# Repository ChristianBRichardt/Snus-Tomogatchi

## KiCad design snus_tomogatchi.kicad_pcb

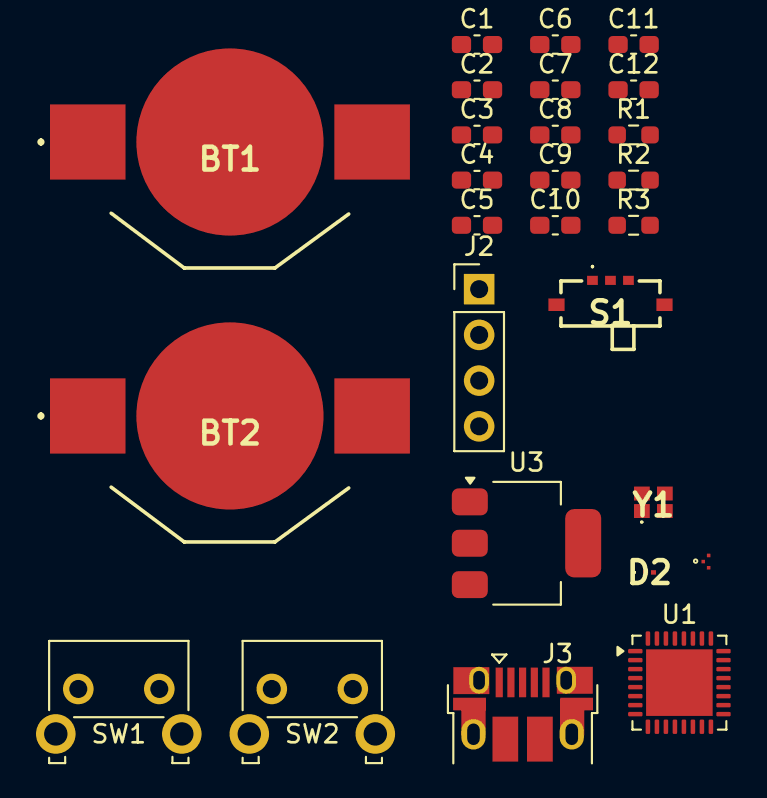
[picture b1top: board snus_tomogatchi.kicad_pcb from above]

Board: 2 copper layers, 27 parts (0 on the bottom side), 15 nets, no tracks yet.

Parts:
BT1, BT2: Battery_Cell; BATHLD007SMTTR
C1, C3, C4, C12: 10uF; C_0603_1608Metric_Pad1.08x0.95mm_HandSolder
C2, C5, C6, C11: 0.1uF; C_0603_1608Metric_Pad1.08x0.95mm_HandSolder
C7: 1uf; C_0603_1608Metric_Pad1.08x0.95mm_HandSolder
C8, C9: C_Small; C_0603_1608Metric_Pad1.08x0.95mm_HandSolder
C10: 1uF; C_0603_1608Metric_Pad1.08x0.95mm_HandSolder
D1: ESD122DMXR; DMX0003A
D2: ESD441DPLR
J2: Conn_01x04; PinHeader_1x04_P2.54mm_Vertical
J3: USB_B_Micro; USB_Micro-B_Amphenol_10103594-0001LF_Horizontal
R1: 10k; R_0603_1608Metric_Pad0.98x0.95mm_HandSolder
R2: 0; R_0603_1608Metric_Pad0.98x0.95mm_HandSolder
R3: 5.6k; R_0603_1608Metric_Pad0.98x0.95mm_HandSolder
S1: SSAJ120100
SW1, SW2: SW_Push; SW_Tactile_SKHH_Angled
U1: ESP32-C3FH4; QFN-32-1EP_5x5mm_P0.5mm_EP3.7x3.7mm
U3: LD1117S33TR_SOT223; SOT-223-3_TabPin2
Y1: ABM11W-40.0000MHZ-6-B1U-T3; ABM11W300000MHZ4B1UT3

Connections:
+3V3: C1.1, C2.2, C3.1, C4.2, C5.1, C6.1, C12.1, J2.2, R1.1, R3.2, U1.2 (VDD3P3), U1.3 (VDD3P3), U1.6 (GPIO2), U1.7 (CHIP_EN), U1.11 (VDD3P3_RTC), U1.14 (GPIO8), U1.17 (VDD3P3_CPU), U1.31 (VDDA), U1.32 (VDDA), U3.2 (VO)
+5V: D2.1, J3.1 (VDD), S1.5 (MP2)
/6V: BT2.1 (+), S1.4 (MP1)
D+: D1.3 (IO2), J3.3 (D+), U1.26 (GPIO19)
D-: D1.2 (IO1), J3.2 (D-), U1.25 (GPIO18)
GND: BT1.2 (-), C1.2, C2.1, C3.2, C4.1, C5.2, C6.2, C7.2, C8.1, C9.2, C10.2, C11.2, C12.2, D1.1 (GND), D2.2, J2.1, J3.5 (GND), SW1.2, SW2.2, U1.33 (GND), U3.1 (GND), Y1.2 (GND_1), Y1.4 (GND_2)
unnamed: BT1.1 (+), BT2.2 (-)
unnamed: C7.1, R1.2, SW1.1
unnamed: C10.1, R3.1, SW2.1, U1.15 (GPIO9)
unnamed: C8.2, U1.29 (XTAL_N), Y1.1 (X1)
unnamed: R2.1, U1.30 (XTAL_P)
unnamed: C9.1, R2.2, Y1.3 (X2)
SCL: J2.3, U1.24 (SPIQ)
SDA: J2.4, U1.23 (SPID)
V_IN: C11.1, S1.3 (COM), U3.3 (VI)
